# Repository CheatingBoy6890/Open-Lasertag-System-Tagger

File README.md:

<div align="center">

###### Partnering with PCBway.
</div>
<br/>

# Open-Lasertag-System

---

https://commons.wikimedia.org/w/index.php?curid=1668938

Warning: This project uses lasers. Be sure to **always** do your own testing by meassuring voltage and current and by looking in datasheets. I am **not** responsible for any injuries you encounter from using this project. Also make sure to wear proper eye-protection.

---

## What is Open-Lasertag-System?

Open-Lasertag-System is our approach to a build Lasertag that can be played anywhere without the need of setting up repeaters or servers, whilst beeing pretty easy to build and extend to fit your needs. It works decentral using a WIFI mesh,so the range and fun extends the more players you have!

Currently the project consists of five parts:

1.  The Taggers are fully functional with features such as different firemodes and score synchronization
2.  The vests are functional and connect wirelessly with the corresponding tagger
3.  Targets : For those who don't want to shoot at each other can just shoot at these. The plan also ist to intergrate the further into the system for modes like capture the Flag
4.  Logger: Counts wich target have been hit by whom
5.  There's a Laser grenade planned

---

## What is this repository?

This is the repository for the taggers of the system. here you'll find all the neccessary files on how to build a tagger your self.

**The instructions on building can be found in the** [**Hardware folder**](https://github.com/CheatingBoy6890/Open-Lasertag-System-Tagger/tree/main/Hardware)

**You can also buy prepackaged set on ebay: https://www.ebay.de/itm/226291836696 (only available in Germany)**

**What you'll need:**

- A 3D-printer capable of printing 20cmx20cm
- Soldering iron
- An ESP 8266 wemos d1 mini
- A piece of LED strip 6 LEDs ws2812b
- OLED 1,3" sh1106 or ssd1306
- At least slightly transparent filament
- PCB or perf matrix board
- Cable
- Pin headers
- Crimp equipment and or breadboard cables
- 16 or 32 Ω 40mm speaker
- 2x electrolytic capacitor min 5V 25uF
- 2x ceramic capacitor min 5V about 0,1uF
- 3x BC547 or other npn transistor with simlar pinout
- 2x Red laserpointer head
- Tsop 4838
- LACO LCU985072A Laserdiode, 50 mW, 980 nm, Ø 5,6 mm
- 2x Button
- Switch
- 2x Resistor 10kΩ
- Resistor 1kΩ
- Resistor 160Ω
- Resistor 12Ω
- Resistor 39Ω
- Resistor 0Ω (Replace with higher resistance when your speaker has below 16Ω)
- Resistor 100kΩ (only PCB V3)
- Resistor 200kΩ (only PCB V3)
- FRX04060F resetable fuse (only PCB V3.1)
- Battery clip
- Battery holder 4 AA batteries
- 6x Screw M4 x40mm
- 3mm diameter piece of metal rod or pipe
- Rubber band

- cover lens (optional)
- Time

  ## Who are we?

  We are two German students. Since we are twins, we build and programm a lot of projects together. We create all of our projects in our free time. Feel free to mail any questions to cyberfox3801@proton.me .
  We want to motivate people to discover what is possible using 3D printing and microcontrollers. \
  The most productive worker of our small group is our cat Susi. 

Congratulations you made it to the end of this readme. If you want this to be longer consider buying us a coffe (https://www.paypal.com/donate/?hosted_button_id=2RZBTA5GMNH6S) so we can make all files longer and better
and don't forget to cuddle your cat!

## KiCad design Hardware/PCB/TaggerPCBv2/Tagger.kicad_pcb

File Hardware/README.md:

<div align="center">

###### Partnering with PCBway.
</div>
<br/>

# Hardware

## General Information

Warning: This project uses lasers. Be sure to **always** do your own testing by meassuring voltage and current and by looking in datasheets. I am **not** responsible for any injuries you encounter from using this project. Also make sure to wear proper eye-protection.

---

**The Tagger runs using 4 1,2V NiMh batteries! Don't use voltages greater than 5V in order to power the Tagger.**

---

Double check that you've soldered the electrolytic capacitors in the right orientation.

---

## 3D Printing

All 3D source files are in the FCstd format. kThey can be opened and edited using <a href ="www.freecad.org/index.php">Freecad</a>.
For printing you can just use the given .stl files.

---

## Perf matrix board

We suggest the perf matrix board version only for people who know what they're doing. If you just want to build your own tagger without changing the layout later we suggest using a PCB.
The schematic for using a breadboard is in the .diy format. These files can be viewed and edited using <a href ="https://bancika.github.io/diy-layout-creator/">DIY Layout creator</a>.

---

## PCB

We created the pcb layout with <a href="https://www.kicad.org/">KiCad</a>. You can easily order really nice high-quality PCBs from our partner [PCBWay](www.pcbway.com) by using the PCBWay plugin in KiCAD following this [turorial](https://www.pcbway.com/blog/News/PCBWay_Plug_In_for_KiCad_3ea6219c.html), exporting the gerber files manually like explained [here](https://www.pcbway.com/blog/help_center/How_to_Generate_Gerber_and_Drill_Files_in_KiCad_7_0_ab0d12bb.html) or use the files in the repository (possibly outdated or not-yet available).

<div align=center>
   
###### Pictures from [Lasertag's Grenade](https://github.com/CheatingBoy6890/Open-Lasertag-System-Grenade) PCB
</div>
---

## The Displays

When buying Oleds from not-so-trustworthy sellers on Amazon or Aliexpress, they might claim to send you an SSD_1306 Oled, but in fact it's one with an SH_1106 controller. You notice that problem, when the pixles on the display are shifted a bit, the you can just change the Display settings to SH_1106 in the icons.h file.

---

## The code

To flash the program to your ESP8266 you need to have <a href="https://code.visualstudio.com/">Visual Studio Code</a> and the platformio extension installed. If you haven't you can follow this tutorial:
<a>https://randomnerdtutorials.com/vs-code-platformio-ide-esp32-esp8266-arduino/</a> To flash an ESP8266 from Windows you might need additional drivers, you'll find a tutorial on this here https://randomnerdtutorials.com/install-esp32-esp8266-usb-drivers-cp210x-windows/

## Building the Tagger

1. Make sure you have got all the required parts 
1. Slice the stl files and print them with a 3d-printer
1. Remove the supports from the 3D printed parts 
1. Flash your ESP8266 with the programm and the sound files
   - Open Visual Studio Code
   - Click Open Folder and choose the Folder you downloaded: 
   - When it askes you, click "trust the authors: 
   - Connect the ESP8266 to your pc and click "upload" to upload the program and then press "build filesystem image" and after that "upload file system image: 
1. Solder the pins to your ESP

   - Make sure that the ESP8266 board is facing the top. (check and cross from pixabay Bild von <a href="https://pixabay.com/de/users/janjf93-3084263/?utm_source=link-attribution&utm_medium=referral&utm_campaign=image&utm_content=2061132">Jan</a> auf <a href="https://pixabay.com/de//?utm_source=link-attribution&utm_medium=referral&utm_campaign=image&utm_content=2061132">Pixabay</a> Bild von <a href="https://pixabay.com/de/users/openclipart-vectors-30363/?utm_source=link-attribution&utm_medium=referral&utm_campaign=image&utm_content=1292787">OpenClipart-Vectors</a> auf <a href="https://pixabay.com/de//?utm_source=link-attribution&utm_medium=referral&utm_campaign=image&utm_content=1292787">Pixabay</a>

1. Solder all components and pin headers to the PCB or matrix board 
1. Solder cables to the buttons,the TSOP and the speaker and crimp sockets at the ends if needed
1. Put the IR-LaserDiode in the casing:
   - Take one of the red laser pointer heads and tear out the laser
   - Grind down about 1mm of the laser pointer head housing
   - Glue the infrared laser in the housing 
1. Solder cables to the LED strip and crimp sockets
1. Solder the red cable of your battery clip to the switch and connect the power pin headers on the PCB
1. Glue the lasers ,the Tsop ,the LED strip ,the speaker and the switch in place
1. Connect all your components to the PCB in the gun housing
1. Cut a 3mm diamter x 35mm piece of metal rod or pipe
1. Put in the trigger using the piece of rod
1. Tense the rubber band between the trigger and the fixture
1. Put in the battery pack with 4 AA 1,2V NiMh batteries
1. Close the Tagger and screw the two parts together
1. Slightly pull the trigger and then turn on power
1. Have fun

## Optional

If you have the PCB_v2 but want to meassure the voltage of the batteries you can use this sketchy solution: 
Don't forget to uncomment the #define CHECK_BATTERY in main.cpp

If you play without vest or you run into receiving issues, add a cover lens on the IR-receiver.

Glue it to one half of the tagger, so you can still open it.

## Tips and Tricks

Making sure the Infrared laser works is possible by checking it with a phone camera. This works with every decent phone, so iPhones obviously do not work.
The 1mw laser can only be seen in darkness.
Be aware that strong infrared lasers can permanently damage your camera sensor.

If your tagger keeps crashing when pressing "shoot" you'll need to go into the onShoot() function and add IRAM_ATTR to every method called here e.g. change
`bool Task::isEnabled() { return iStatus.enabled; }`
in .pio/libdeps/d1_mini/TaskScheduler/src/TaskScheduler.h to:
`bool IRAM_ATTR Task::isEnabled() { return iStatus.enabled; }`
Do this for the Task::restart() method and al other as well.

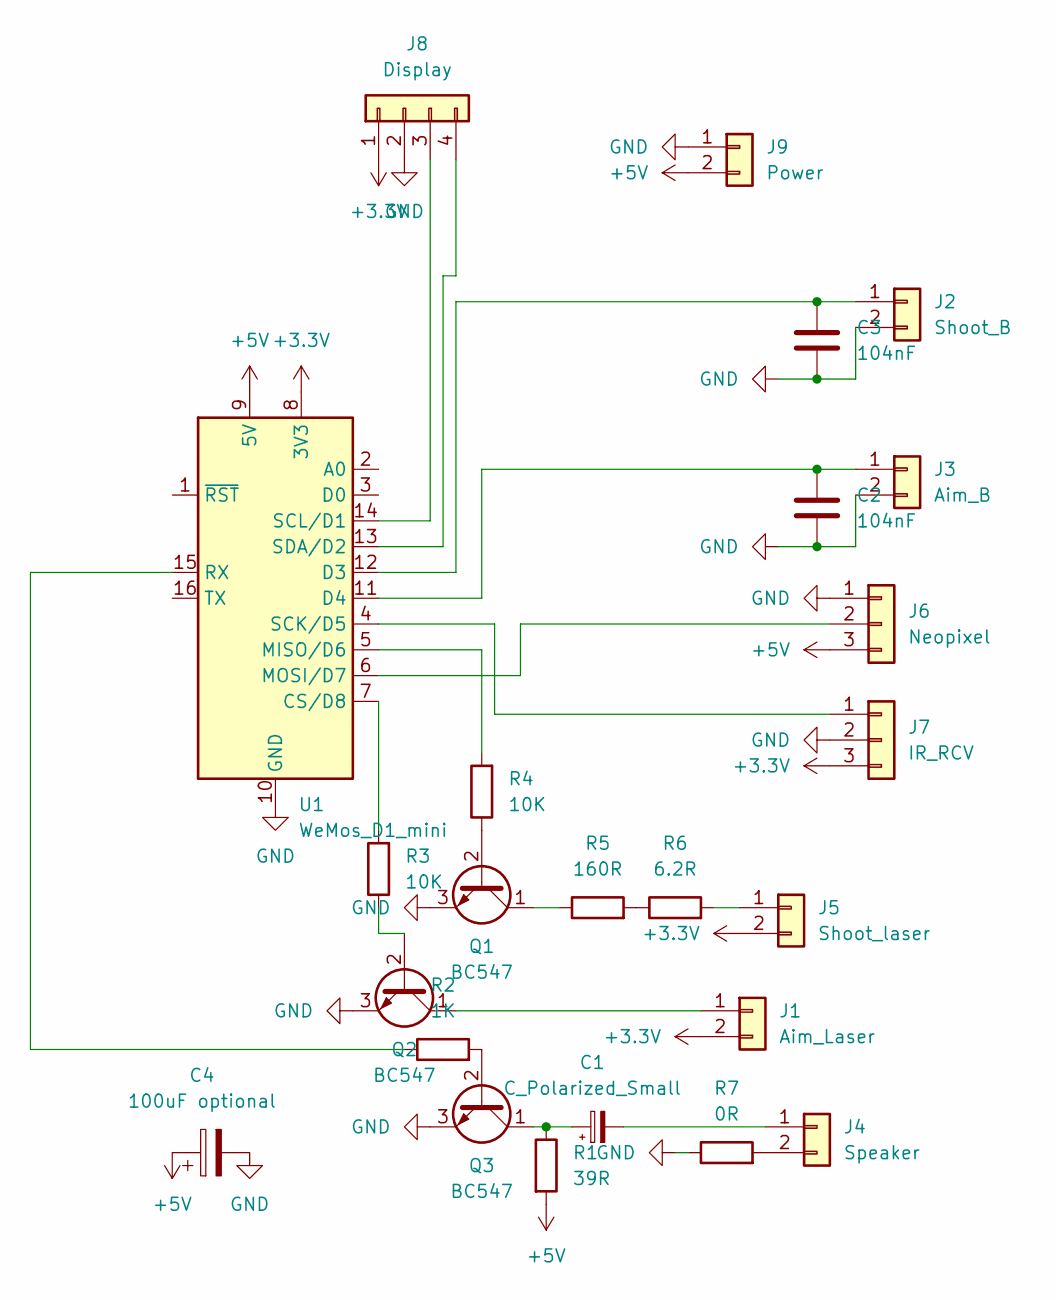
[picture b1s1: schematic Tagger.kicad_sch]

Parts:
C1: C_Polarized_Small; CP_Radial_D4.0mm_P2.00mm
C2, C3: 104nF; C_Disc_D5.0mm_W2.5mm_P2.50mm
C4: 100uF optional; CP_Radial_D6.3mm_P2.50mm
J1: Aim_Laser; PinHeader_1x02_P2.54mm_Vertical
J2: Shoot_B; PinHeader_1x02_P2.54mm_Vertical
J3: Aim_B; PinHeader_1x02_P2.54mm_Vertical
J4: Speaker; PinHeader_1x02_P2.54mm_Vertical
J5: Shoot_laser; PinHeader_1x02_P2.54mm_Vertical
J6: Neopixel; PinHeader_1x03_P2.54mm_Vertical
J7: IR_RCV; PinHeader_1x03_P2.54mm_Vertical
J8: Display; PinHeader_1x04_P2.54mm_Vertical
J9: Power; PinHeader_1x02_P2.54mm_Vertical
Q1, Q2, Q3: BC547; TO-92_Inline
R1: 39R; R_Axial_DIN0204_L3.6mm_D1.6mm_P7.62mm_Horizontal
R2: 1K; R_Axial_DIN0204_L3.6mm_D1.6mm_P7.62mm_Horizontal
R3, R4: 10K; R_Axial_DIN0204_L3.6mm_D1.6mm_P7.62mm_Horizontal
R5: 160R; R_Axial_DIN0204_L3.6mm_D1.6mm_P7.62mm_Horizontal
R6: 6.2R; R_Axial_DIN0204_L3.6mm_D1.6mm_P7.62mm_Horizontal
R7: 0R; R_Axial_DIN0204_L3.6mm_D1.6mm_P7.62mm_Horizontal
U1: WeMos_D1_mini; WEMOS_D1_mini_light

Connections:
+3.3V: J1.2, J5.2, J7.3, J8.1, U1.8 (3V3)
+5V: C4.1, J6.3, J9.2, R1.2, U1.9 (5V)
GND: C2.1, C3.1, C4.2, J2.2, J3.2, J6.1, J7.2, J8.2, J9.1, Q1.3 (E), Q2.3 (E), Q3.3 (E), R7.1, U1.10 (GND)
unnamed: J1.1, Q2.1 (C)
unnamed: C3.2, J2.1, U1.12 (D3)
unnamed: C2.2, J3.1, U1.11 (D4)
unnamed: C1.2, J4.1
unnamed: J4.2, R7.2
unnamed: J5.1, R6.2
unnamed: J6.2, U1.6 (MOSI/D7)
unnamed: J7.1, U1.4 (SCK/D5)
unnamed: J8.3, U1.14 (SCL/D1)
unnamed: J8.4, U1.13 (SDA/D2)
unnamed: Q1.2 (B), R4.1
unnamed: Q1.1 (C), R5.1
unnamed: Q2.2 (B), R3.1
unnamed: Q3.2 (B), R2.2
unnamed: C1.1, Q3.1 (C), R1.1
unnamed: R5.2, R6.1
unnamed: R3.2, U1.7 (CS/D8)
unnamed: R4.2, U1.5 (MISO/D6)
unnamed: R2.1, U1.15 (RX)

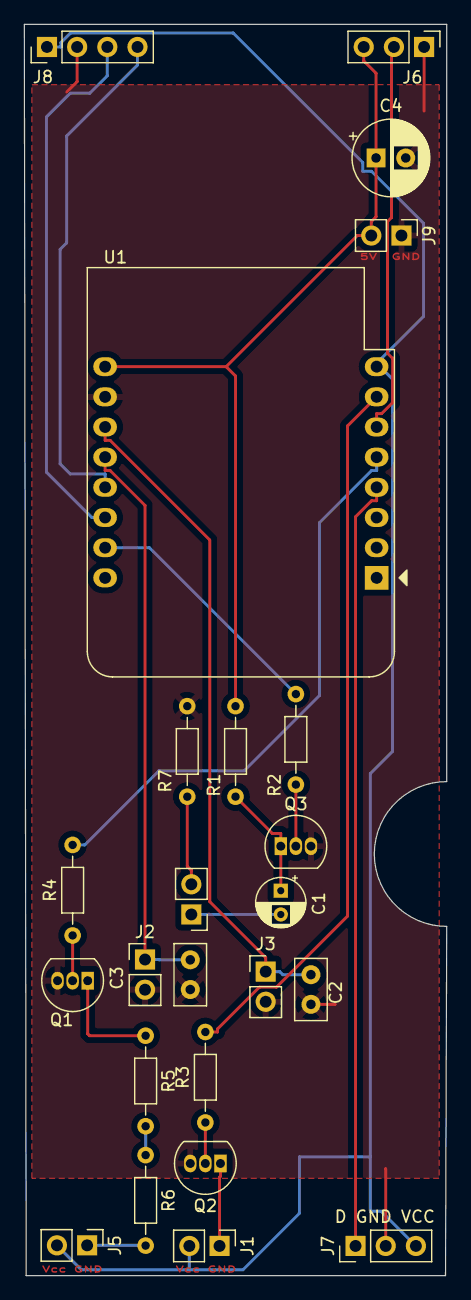
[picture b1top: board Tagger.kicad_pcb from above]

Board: 2 copper layers, 35.6 x 105.3 mm, 24 parts (0 on the bottom side), 22 nets.

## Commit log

2024-02-07 First commit. The code from PWA_Lasertag mostly ported to the ESP8266 because it's cheaper.
2024-02-08 Made drawing bullets parametric so you can easyly change the max amount of bullets.
2024-02-08 Made drawing bullets parametric and prettied up the code for reloading.
2024-04-15 Modified some things somewhat working now.
    After a random bit of time the scheduler stops scheduling even when soft-disabling the painlessmesh( another scheduler for the mesh) but the problem persits.
    This commit is to save some work when trying to completely disable the mesh.
2024-04-17 First fully working version (Teamsync missing)
    No crashes so far works like a charm.
2024-04-20 Added 3D print file
    One half of the tagger has been added.
    Also some icons for different weapons.
2024-06-27 Changed the sounds to be in Wav Format so the buffer can be smaller.
2024-07-21 Create LICENSE
2024-07-22 Added files for 3D printing and PCB/perf board. Removed Tagger_fixed_Rounded_Somethings_3 .
2024-07-22 Enabled Team score sync
2024-07-25 Update main.cpp
    Added license to main.cpp
2024-07-25 Update neopixel_config.h
    License for all src files
2024-07-25 Update README.md
    Added Laser injuries warning
2024-07-25 Added target and logger programm
2024-07-25 Added PCB V3 and moved the perf board schematic out of the PCB folder.
2024-07-25 Moved Target and Logger to their own Repository
    Fixed the copyright for each source file.
2024-07-25 Added Linus Hille to the copyright
2024-07-25 Added README into Hardware
2024-07-27 Changed the default display to SSD_1306 and changed the ESP8266 Audio Library to use <I2S.h> instead of <i2s.h> so it works again. Next thing to do is to get the sound working with a newer version of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
2024-07-27 Removed the old version of ESP8266 Audio and replaced it with the one installable from platformio
2024-07-27 Changed default Display back to SH_1106 because cheap aliexpress Display which claim to use SSD_1306 Controllers actually use these.
    Added STL file versions of the fcstd files.
2024-07-27 Added better explaination of how to upload the code.
2024-07-28 Added pictures to almost every step
2024-07-28 Added link to the readme in the hardware folder.
2024-07-29 Added a donation link
2024-07-29 Aktualisieren von README.md
2024-07-30 Added the PCBv3.1
2024-07-30 Added instructions for sketchy voltage divider
2024-07-30 Added the code to meassure the batteries.
2024-08-11 -Added compatibility to connect to the vest -Put things in F() macros to squeeze out a little bit of ram.
2024-08-12 Made machine gun shoot slower Fixed teamselection to not use timer, but instead wait until trigger is released.
2024-08-13 Fixes random crashes due to some interrupt functions not beeing in IRAM Added an explaination in the Hardware readme so people can fix it them selves unignored the TaskScheduler folder so hopefully p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
2024-08-15 Tried fixing the crash taht happens when something connects to the mesh, wasn't able to.
2024-08-15 Fixes all crashes so far, first fully working version
2024-09-03 Added PCBwayImage
2024-09-03 Added PCBWay advert
2024-10-06 Added the new bootup sound, which needs to be implemented. Changed To LittleFs since SPIFFS deprecated for ESP8266
2025-01-11 Made a plan for a easier Audio Amplifier circuit.
